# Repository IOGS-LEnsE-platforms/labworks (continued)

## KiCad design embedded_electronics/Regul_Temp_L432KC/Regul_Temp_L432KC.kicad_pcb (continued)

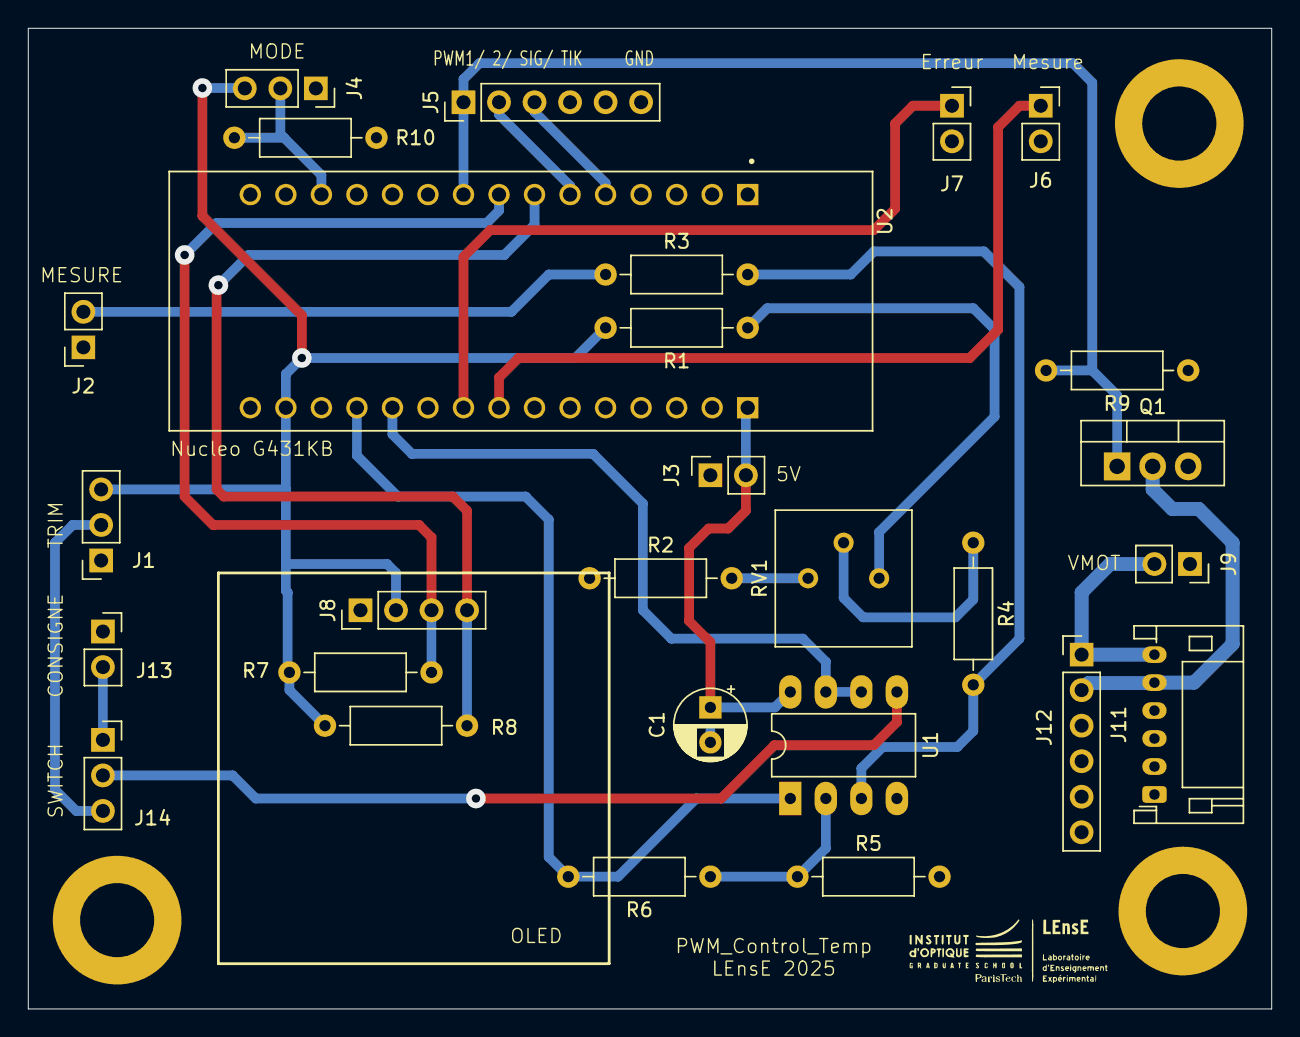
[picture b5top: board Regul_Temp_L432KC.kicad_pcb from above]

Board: 2 copper layers, 88.9 x 70.1 mm, 28 parts (0 on the bottom side), 25 nets.

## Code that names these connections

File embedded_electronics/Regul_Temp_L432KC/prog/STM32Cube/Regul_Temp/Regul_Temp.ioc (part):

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Mcu.Name=STM32L432K(B-C)Ux
Mcu.Package=UFQFPN32
Mcu.UserName=STM32L432KCUx
PA0.GPIOParameters=GPIO_Label
PA0.GPIO_Label=MESURE
PA0.Signal=ADCx_IN5
PA1.GPIOParameters=GPIO_Label
PA1.GPIO_Label=CONSIGNE
PA1.Signal=ADCx_IN6
PA11.GPIOParameters=GPIO_Label
PA11.GPIO_Label=MODE
PA11.Signal=GPIO_Input
PA12.GPIOParameters=GPIO_Label
PA12.GPIO_Label=SIGNE
PA12.Signal=GPIO_Output
PA13\ (JTMS-SWDIO).GPIOParameters=GPIO_Label
PA13\ (JTMS-SWDIO).GPIO_Label=SWDIO
PA13\ (JTMS-SWDIO).Mode=Serial_Wire
PA13\ (JTMS-SWDIO).Signal=SYS_JTMS-SWDIO
PA14\ (JTCK-SWCLK).GPIOParameters=GPIO_Label
PA14\ (JTCK-SWCLK).GPIO_Label=SWCLK
PA14\ (JTCK-SWCLK).Mode=Serial_Wire
PA14\ (JTCK-SWCLK).Signal=SYS_JTCK-SWCLK
PA15\ (JTDI).GPIOParameters=GPIO_Label
PA15\ (JTDI).GPIO_Label=VCP_RX
PA15\ (JTDI).Signal=USART2_RX
PA2.GPIOParameters=GPIO_Label
PA2.GPIO_Label=HORLOGE
PA2.Signal=GPIO_Output
PA4.GPIOParameters=GPIO_Label
PA4.GPIO_Label=ERREUR
PA4.Signal=COMP_DAC11_group
PA5.GPIOParameters=GPIO_Label
PA5.GPIO_Label=MESURE
PA5.Signal=COMP_DAC12_group
PB0.GPIOParameters=GPIO_Label
PB0.GPIO_Label=PWM2
PB0.Mode=PWM Generation2 CH2N
PB0.Signal=TIM1_CH2N
PB1.GPIOParameters=GPIO_Label
PB1.GPIO_Label=PWM_MOT
PB1.Mode=PWM Generation3 CH3N
PB1.Signal=TIM1_CH3N
PB3\ (JTDO-TRACESWO).GPIOParameters=GPIO_Label
PB3\ (JTDO-TRACESWO).GPIO_Label=LD3 [Green]
PB3\ (JTDO-TRACESWO).Signal=GPIO_Output
PC14-OSC32_IN\ (PC14).Mode=LSE-External-Oscillator
PC14-OSC32_IN\ (PC14).Signal=RCC_OSC32_IN
PC15-OSC32_OUT\ (PC15).Mode=LSE-External-Oscillator
PC15-OSC32_OUT\ (PC15).Signal=RCC_OSC32_OUT
RCC.HSE_VALUE=8000000
RCC.SYSCLKFreq_VALUE=80000000
RCC.SYSCLKSource=RCC_SYSCLKSOURCE_PLLCLK
board=NUCLEO-L432KC
boardIOC=true

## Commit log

2025-03-29 First Commit / Move from Maquettes_LEnsE in embedded
2025-03-30 Update CubeIDE workspace
2025-03-31 Update FIR filter
2025-05-09 Update Maquette Filtre Numérique v2
2025-05-20 Test FIR Filter on G431KB - Cube IDE
2025-05-21 Update FIR Filter on G431KB
2025-05-22 Update Temp Control PWM for CCS
2025-05-22 Update gitignore
2025-05-22 Adding doc to Temp regulation platform
2025-05-22 Update PCB of Regulation platform
2025-05-22 Update Regulation temperature
2025-05-22 Adding STM32Cube program for Regul Temp labwork
2025-05-23 Update Regul temp
2025-05-23 Adding Hello_L432KC (to test !)
2025-05-23 Adding Bingoptik in Stuffs - v2.1
2025-05-26 Update BingOptik v2 / Test program on Nucleo L432KC - to test !
2025-05-27 Update Bingoptik program
2025-06-02 Update Bingoptik v2 - New test with numbers
2025-06-03 Update Regul Temp Platform
2025-06-03 Update Regul Temp / Debugging LCD screen and test of Follower
2025-06-03 Update Bingoptik v2 / Adding LCD on F469i-Disco
2025-06-04 Update Regul CCS
2025-06-08 Update Bingoptik / LCD
2025-06-09 Update STM32
2025-06-12 Test Bingoptik LCD
2025-06-16 Update BingOptik
2025-06-17 Update Prog
2025-06-17 Update BingOptik - Test with 2 images
2025-06-19 Update Ignore
2025-06-19 Update Regul Temp L432 / Modif Prog - FInal version
2025-08-25 Update G431KB filter
2025-08-26 Update BingOptik 2
2025-08-26 Update BingOptik - TO TEST - mode change
2025-08-27 Update LCD Paint on STM32CubeIDE
2025-08-29 Update BingOptik / Random value with ADC + 2 modes
2025-08-31 Update Bingoptik LCD - final version to test
2025-09-01 Update Bingo with tuto on WS2812 / HAL
2025-09-01 Update BingOptik / Include WS2812 (not working !! to test)
2025-09-01 Retrait des dossiers .metadata de GIT
2025-09-02 Update BingOptik / Test at office
2025-09-02 No UPdate
2025-09-02 Update BingOptik / autonomous compiled version
2025-09-04 Update Bingo
2025-09-05 Update BingOptik / STM32 HAL lib for WS2812 leds
2025-09-08 Update BingOptik 2 / 2 strips of leds (to test)
2025-09-11 Update BingOptik v2 / Final version to test
2025-09-12 UPdate BingOptik on L469i-Disco
2025-09-15 Update BingOptik v2 - TIM2 ok with WS2812
    Mode management to implement
2025-09-16 Update BingOptik v2 / Final version
    To test
2025-09-26 Adding AM_modulation_fiber project
2025-09-26 Update AM_modulation_filter
2025-09-26 Update AM Modulation and Fiber transmission / demo and labwork
2025-09-29 Update AM_Modulation_Fiber circuit
2025-09-29 Update AM_Modulation_Fiber
2025-09-30 Update AM Modulation Fiber / New PCB
2025-09-30 Update AM modulation documentation
2025-11-03 Adding Colorimetry programs
2025-11-04 Adding RaspPi project with LED matrix
2025-11-04 Update LED Matrix project with RaspPi
2025-11-06 Update ArtScience / Matrix LED controlling
2025-11-06 Add monochromator documentation
2025-12-08 Update Joy It Car
2025-12-14 Add platforms test codes (joy it, 2 wheels...)
2025-12-14 change dir names
2025-12-14 Update JoyIt Car robot test codes
2025-12-15 Update JoyIt Car test codes
2026-01-29 Update Robot
2026-03-16 Remove old board
2026-03-16 Add New board for OptoElec / Main board
2026-03-16 Update OptoElec Board / Main board
2026-03-16 Minor update
2026-03-16 Update Opto new boards / Main and PhotoSlave
2026-03-16 Minor
2026-03-17 Update Opto Boards / To change : var +15V and var -15V ?
2026-03-17 Small Update
2026-03-18 Create Opto Board Main D25 / new connector test
2026-03-18 Update OptoBoard / D25 version
2026-03-18 Update Opto Board D25
2026-03-20 Update Opto D25
2026-04-19 Update Opto / Master and PhD Slave boards
2026-04-19 Create New Opto Elec board / control loop for led
2026-04-20 Add Opto Board / Illuminance Control loop
2026-04-20 Update Opto Board / Illuminance closed loop system
2026-04-20 Update Opto Board / Update Illuminance Control - analog circuit PID
2026-04-20 Update Opto Boards / Finish Illuminance Control Syst.
2026-04-21 Update OPTO Board / Finish Main - Photodetec - Control
2026-04-21 Update Opto Board / Update Control loop
2026-05-03 Update PDF for Opto Board / D25
2026-05-21 Update Opto Boards / Phd_slave_d25 with CT for transimpedance
